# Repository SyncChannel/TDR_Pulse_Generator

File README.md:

# TDR_Pulse_Generator
A simple Time Domain Reflectometer (TDR) Pulse Generator.

This board is NOT yet tested. Check back in a few weeks for a full write-up.

http://syncchannel.blogspot.com

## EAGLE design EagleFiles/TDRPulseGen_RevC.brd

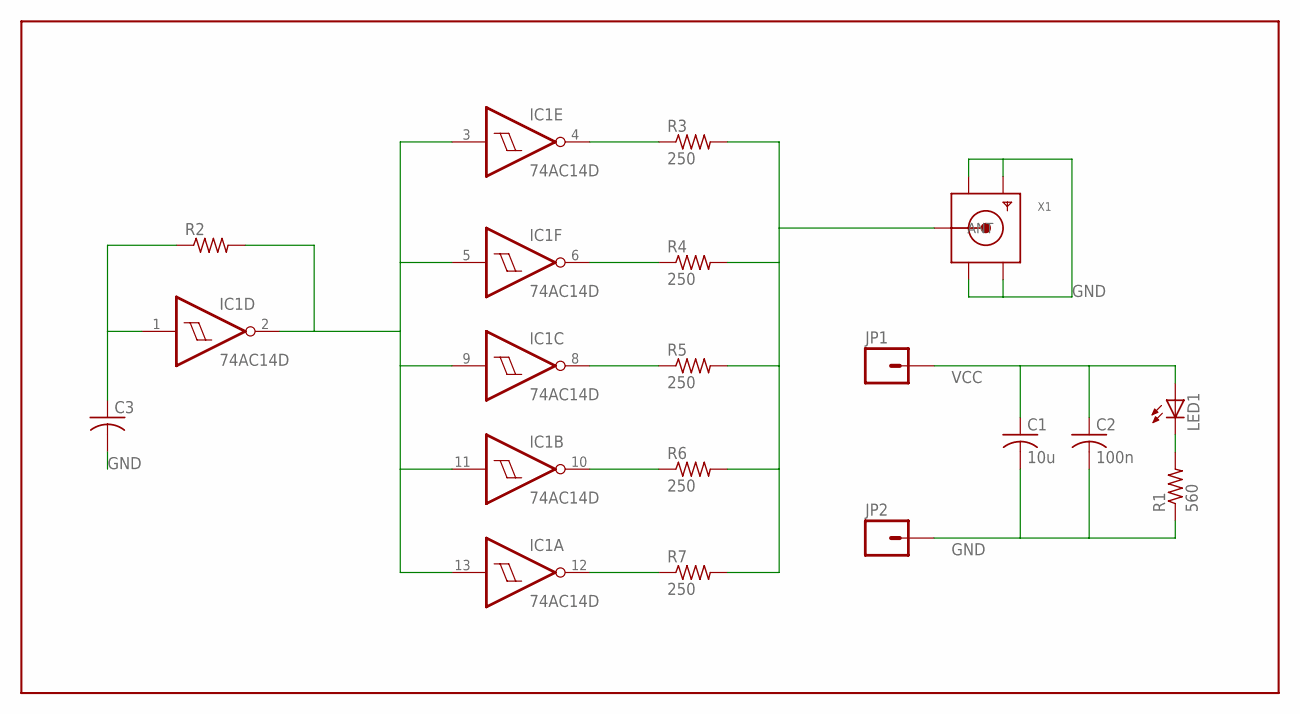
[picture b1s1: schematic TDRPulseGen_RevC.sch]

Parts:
C1: 10u; C0805
C2: 100n; C0805
C3: C-USC0805; C0805
IC1: 74AC14D; SO14
JP1, JP2: M01PTH; 1X01
LED1: LEDCHIPLED_0805; CHIPLED_0805
R1: 560; R0805
R2: R-US_R0805; R0805
R3, R4, R5, R6, R7: 250; R0805
X1: SMACONNECTOR; SMA90_DIP

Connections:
GND: C1.2, C2.2, C3.2, IC1.7 (GND), JP2.1, R1.1, X1.GND1, X1.GND2, X1.GND3, X1.GND4
unnamed: IC1.2 (O), IC1.3 (I), IC1.5 (I), IC1.9 (I), IC1.11 (I), IC1.13 (I), R2.2
unnamed: C3.1, IC1.1 (I), R2.1
unnamed: IC1.4 (O), R3.1
unnamed: LED1.C, R1.2
unnamed: IC1.6 (O), R4.1
unnamed: IC1.8 (O), R5.1
unnamed: IC1.10 (O), R6.1
unnamed: IC1.12 (O), R7.1
unnamed: R3.2, R4.2, R5.2, R6.2, R7.2, X1.ANTENNA (ANT)
VCC: C1.1, C2.1, IC1.14 (VCC), JP1.1, LED1.A

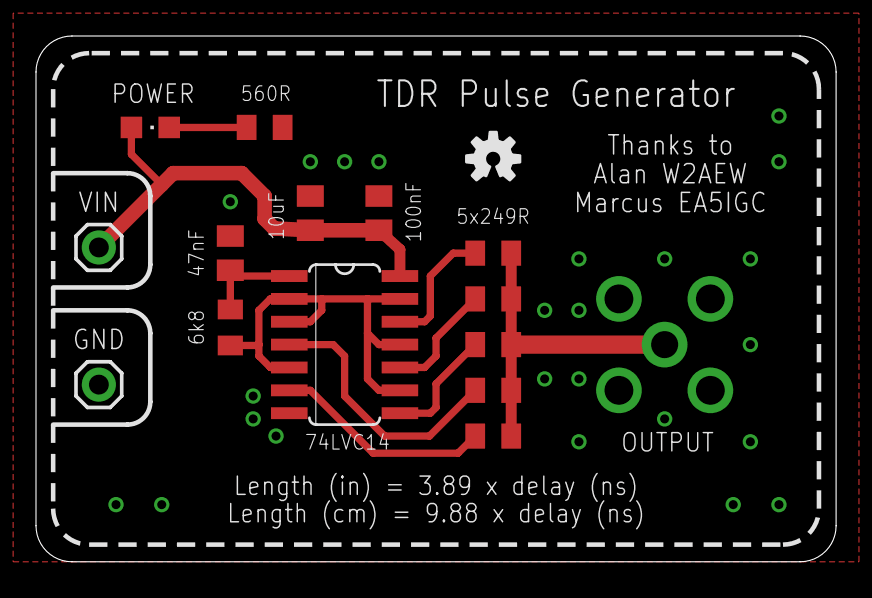
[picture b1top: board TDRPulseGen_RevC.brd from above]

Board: 2 copper layers, 44.5 x 29.2 mm, 16 parts (0 on the bottom side), 11 nets.

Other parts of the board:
U$2: OSHW-LOGO-S

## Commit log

2016-07-02 :circus_tent: Added .gitattributes & .gitignore files
2016-07-02 Added Eagle files
2016-07-02 Added License

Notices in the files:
parts and their libraries:
SparkFun-Connectors: Licensing: Creative Commons ShareAlike 4.0 International - https://creativecommons.org/licenses/by-sa/4.0
